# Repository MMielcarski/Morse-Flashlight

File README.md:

# Morse-Flashlight
Flashlight with built-in Morse code coder and decoder

Full documentation (in Polish): https://github.com/MMielcarski/Morse-Flashlight/blob/master/v_1/Documentation/morse-flashlight-1_0.pdf

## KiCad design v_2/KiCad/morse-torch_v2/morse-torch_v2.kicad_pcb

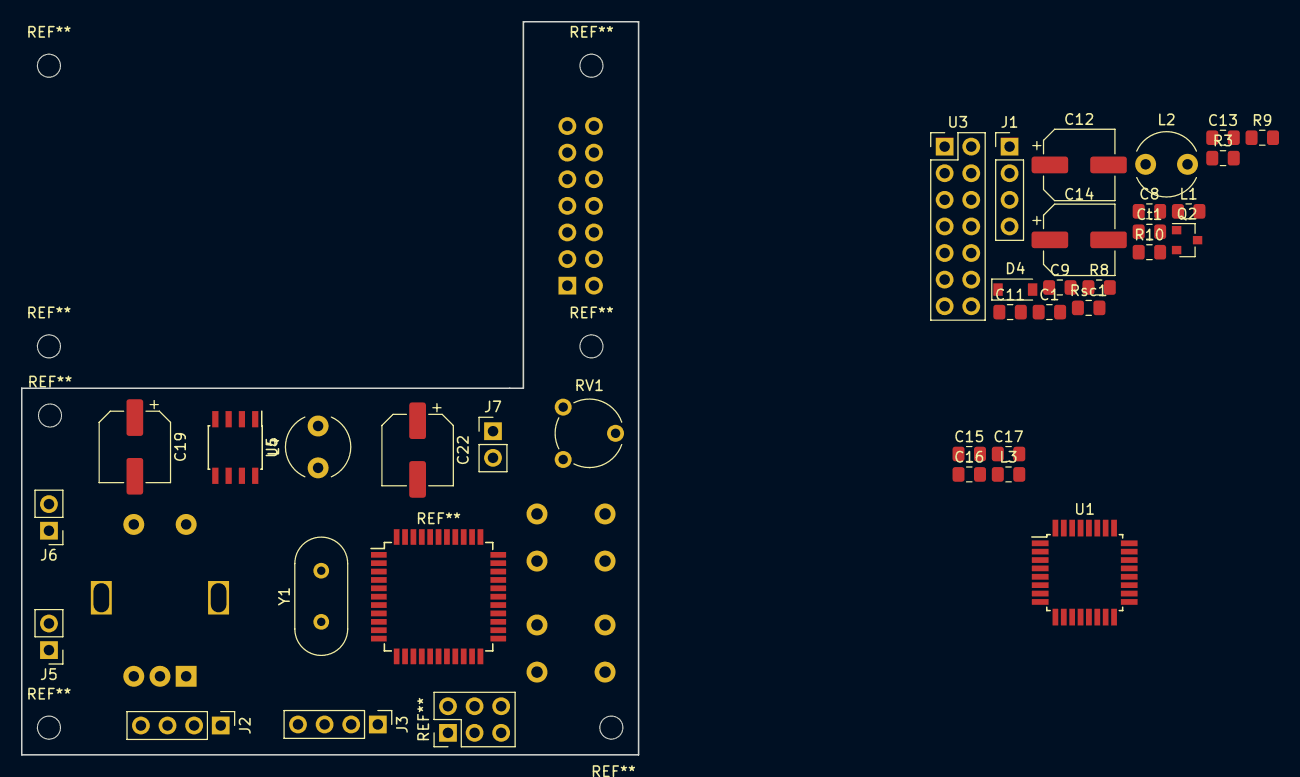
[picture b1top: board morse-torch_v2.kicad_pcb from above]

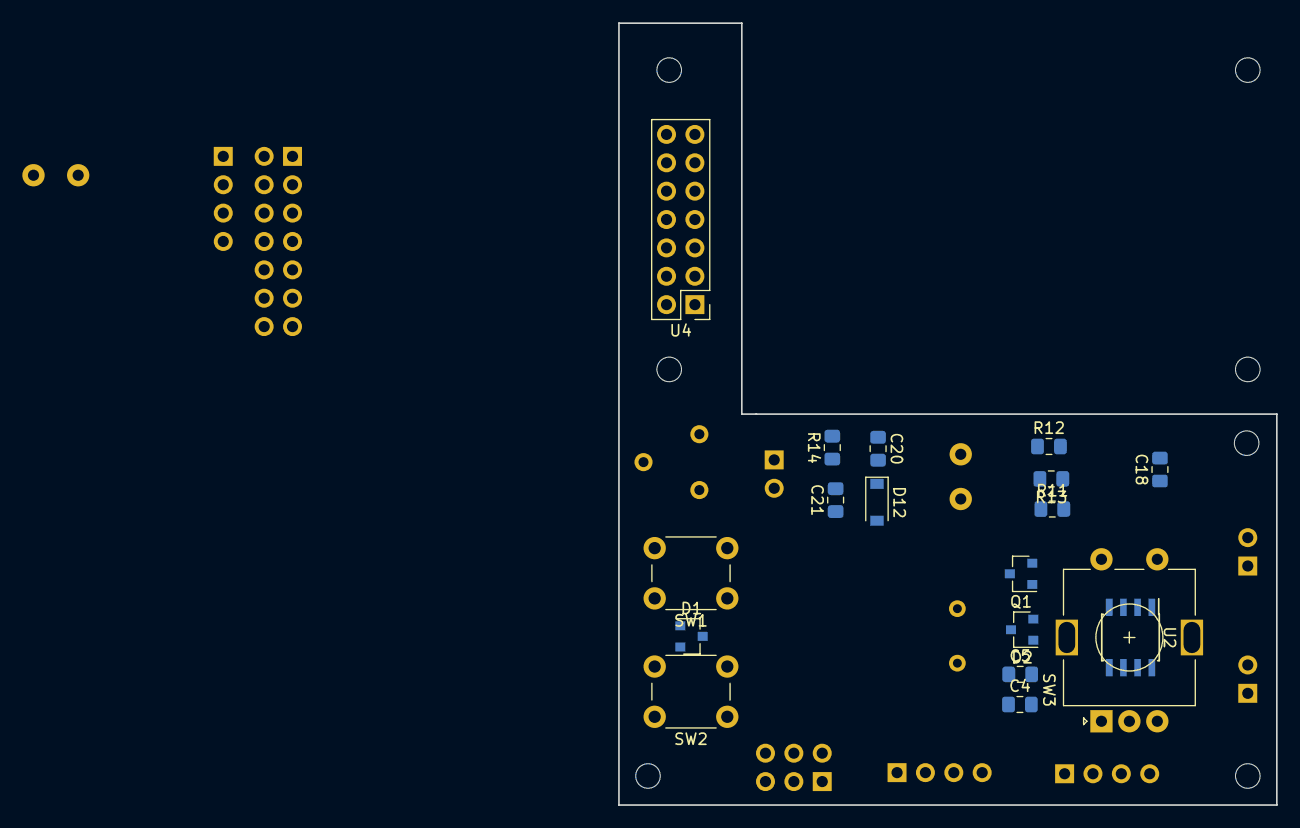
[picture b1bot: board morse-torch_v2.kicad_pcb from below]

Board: 2 copper layers, 58.9 x 70.0 mm, 53 parts (18 on the bottom side), 42 nets, no tracks yet.

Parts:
C1, C4, C5, C15, C16, C17: 100nF; C_0805_2012Metric_Pad1.15x1.40mm_HandSolder
C8, C9: 22pF; C_0805_2012Metric_Pad1.15x1.40mm_HandSolder
C11, C13, C18, C21: 100n; C_0805_2012Metric_Pad1.15x1.40mm_HandSolder
C12, C14, C19, C22: 100u; CP_Elec_6.3x5.4
C20: 470p; C_0805_2012Metric_Pad1.15x1.40mm_HandSolder
Ct1: 470p; C_0805_2012Metric_Pad1.15x1.40mm_HandSolder
D1, D2: BAT54C; SOT-23
D4, D12: MBR0520; D_SOD-123
J1: USART; PinHeader_1x04_P2.54mm_Vertical
J2: AVR-ISP-6; PinHeader_1x04_P2.54mm_Vertical
J3: I2C; PinHeader_1x04_P2.54mm_Vertical
J5: LIGHT; PinHeader_1x02_P2.54mm_Vertical
J6: PWR; PinHeader_1x02_P2.54mm_Vertical
J7: Microsemi_FlashPro-JTAG-10; PinHeader_1x02_P2.54mm_Vertical
L1, L3: 10uH; L_0805_2012Metric_Pad1.15x1.40mm_HandSolder
L2: 82u; L_Radial_D6.0mm_P4.00mm
L4: 10u; L_Radial_D6.0mm_P4.00mm
Q1, Q2: BC817; SOT-23
R3, R11: 10k; R_0805_2012Metric_Pad1.15x1.40mm_HandSolder
R8: 130k; R_0805_2012Metric_Pad1.15x1.40mm_HandSolder
R9, R13, R14: 100k; R_0805_2012Metric_Pad1.15x1.40mm_HandSolder
R10: 390k; R_0805_2012Metric_Pad1.15x1.40mm_HandSolder
R12: 33k; R_0805_2012Metric_Pad1.15x1.40mm_HandSolder
RV1: 10k; Potentiometer_Piher_PT-6-V_Vertical
Rsc1: 1; R_0805_2012Metric_Pad1.15x1.40mm_HandSolder
SW1, SW2: SW_Push; SW_PUSH_6mm
SW3: Rotary_Encoder_Switch; RotaryEncoder_Alps_EC11E-Switch_Vertical_H20mm
U1: ATmega328P-AU; TQFP-32_7x7mm_P0.8mm
U2: 24LC128; SOIC-8_3.9x4.9mm_P1.27mm
U3: NHD-0420H1Z; PinHeader_2x07_P2.54mm_Vertical
U4: MC34063AD; PinHeader_2x07_P2.54mm_Vertical
U5: ATmega32-16AU; SOIC-8_3.9x4.9mm_P1.27mm
Y1: Crystal; Crystal_HC49-U_Vertical

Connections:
5V-converter: C21.1, C22.2, D12.1, R14.2
+5V: C4.1, C16.1, J1.2, J2.2, J3.2, L1.1, L3.1, R3.1, R11.1, RV1.3, U1.4, U1.6, U1.18, U2.8, U3.2, U5.5
ADC0: C18.1, C19.2, J5.2, J6.2, U1.23
BUTTON_1: D1.1, SW2.2, U1.12
BUTTON_2: D1.2, SW1.2, U1.13
ENC_A: D2.2, U1.14
ENC_B: D2.1, U1.22
ENC_BUTTON: SW3.S1, U1.19
GND: C1.1, C4.2, C5.2, C8.2, C9.2, C11.2, C12.1, C13.2, C14.1, C15.1, C16.2, C17.2, C18.2, C19.1, C20.2, C21.2, C22.1, Ct1.2, J1.1, J3.1, Q1.2, Q2.2, R8.1, R12.1, RV1.1, SW1.1, SW2.1, SW3.C, SW3.S2, U1.3, U1.5, U1.21, U2.4, U3.1, U3.5, U4.2, U4.4
LCD_DATA4: U1.2, U3.11
LCD_DATA5: U1.9, U3.12
LCD_DATA6: U1.10, U3.13
LCD_DATA7: U1.11, U3.14
LCD_E: U1.25, U3.6
LCD_RS: U1.26, U3.4
MISO: J2.1, U1.16
MOSI: J2.4, U1.15
unnamed: C1.2, U1.20
unnamed: C5.1, L1.2
unnamed: C11.1, C12.2, J6.1, Rsc1.2, U4.6
unnamed: C17.1, L3.2
unnamed: Ct1.1, U4.3
unnamed: D1.3, D2.3, U1.32
unnamed: D4.2, L2.2, U4.1
unnamed: D12.2, L4.2
unnamed: J5.1, Q2.3
unnamed: L2.1, R9.1, Rsc1.1, U4.7
unnamed: L4.1, R13.1
unnamed: R9.2, U4.8
unnamed: R8.2, R10.1, U4.5
unnamed: R12.2, R14.1
unnamed: RV1.2, U3.3
RESET: R3.2, R11.2, U1.29, U5.4
RXD: J1.4, U1.30
SCK: J2.3, U1.17
SCL: J3.4, U1.28, U2.6
SDA: J3.3, U1.27, U2.5
TXD: J1.3, U1.31
Uout=+5V: C13.1, C14.2, D4.1, R10.2
XTAL1: C8.1, U1.7, U5.8, Y1.1
XTAL2: C9.1, U1.8, U5.7, Y1.2
write-protection: U1.1, U2.7

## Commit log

2018-03-24 Create temp
2018-03-24 Create tempfile
2018-03-24 Create tempsrc
2018-03-24 first commit local
2018-03-24 pierwsza zmiana testowa
2018-03-25 test drugi
2018-04-06 kicad schematic
2018-04-10 dir structure change and src files replacement for up to date version with broadcast speed change feature
2018-04-13 latex documentation and photos
2018-04-14 latex documentation ready
2018-04-15 documentatin v. 1.0 ready for printing
2018-05-23 latex code display enchancement with minted package
2018-05-23 updated pdf files
2018-12-08 morse-torch v2 initial commit
2018-12-15 started pcb design, step-up converter needs approval
2019-02-24 changed uc to atmega32, added jtag interface, roughly set up final layout
